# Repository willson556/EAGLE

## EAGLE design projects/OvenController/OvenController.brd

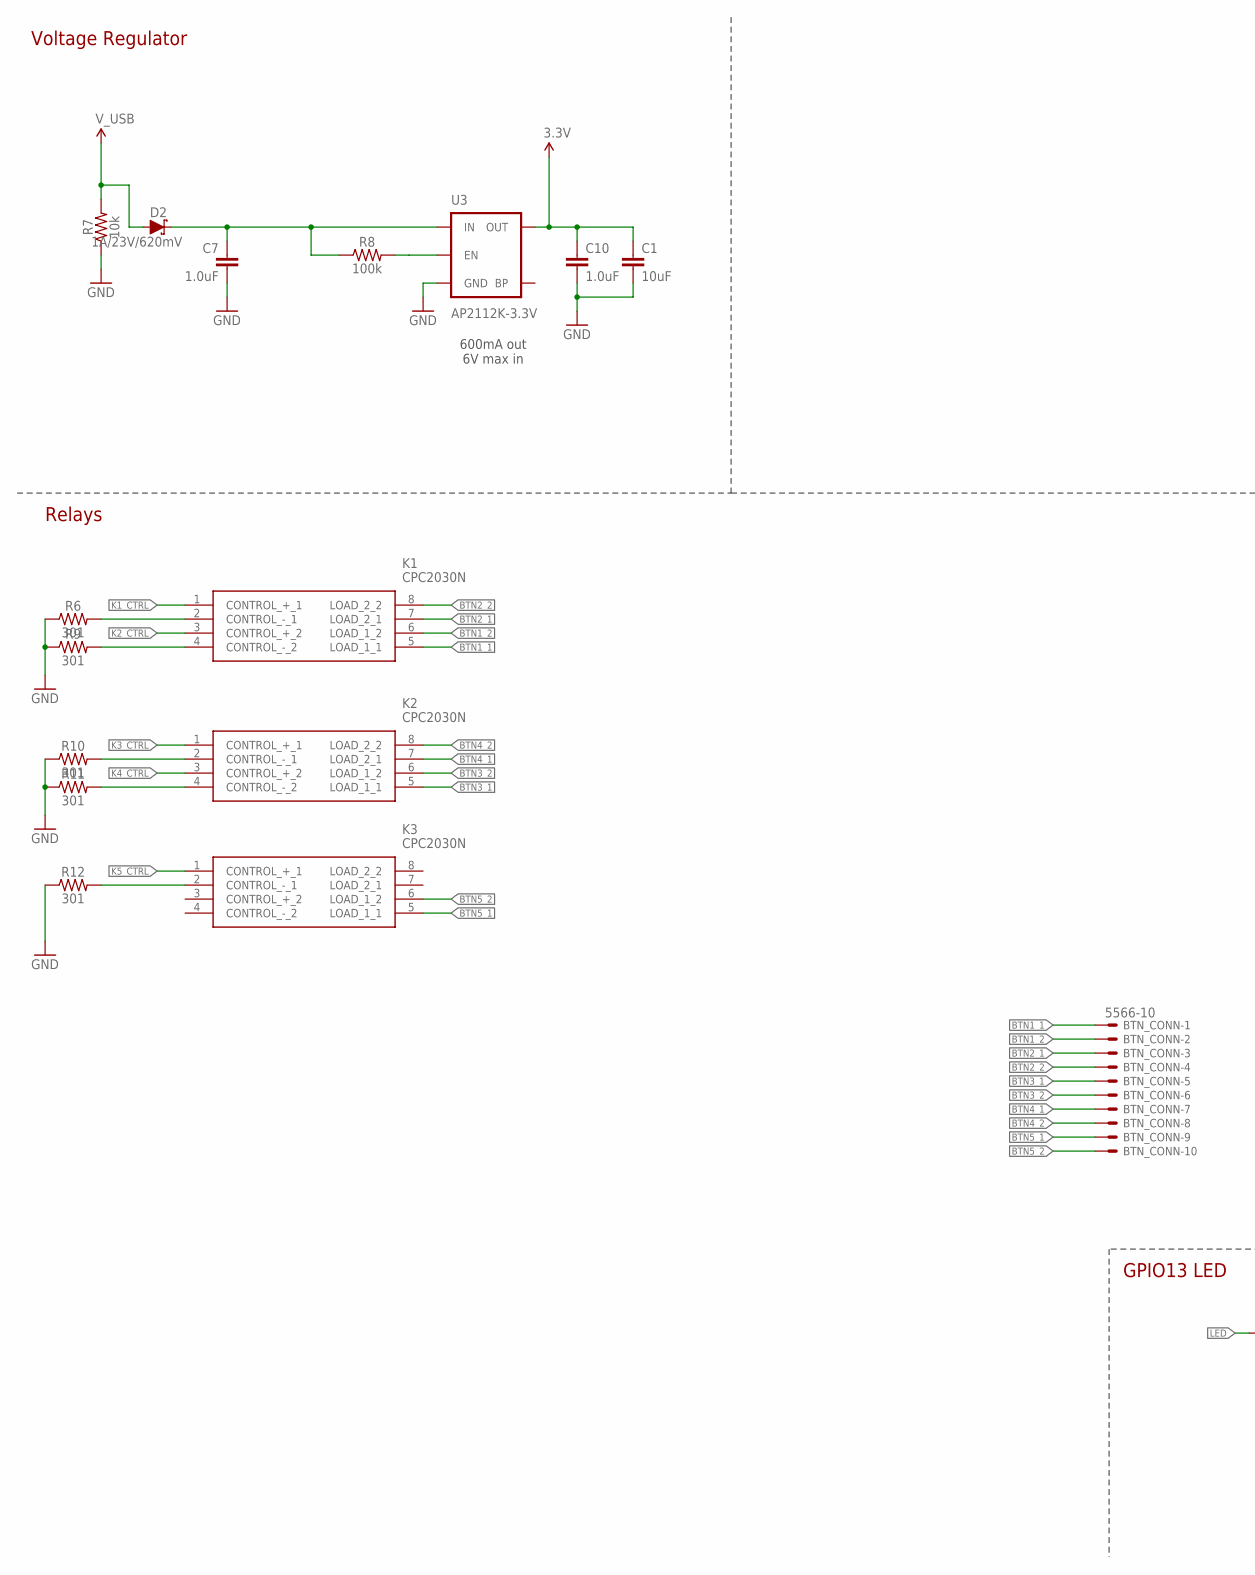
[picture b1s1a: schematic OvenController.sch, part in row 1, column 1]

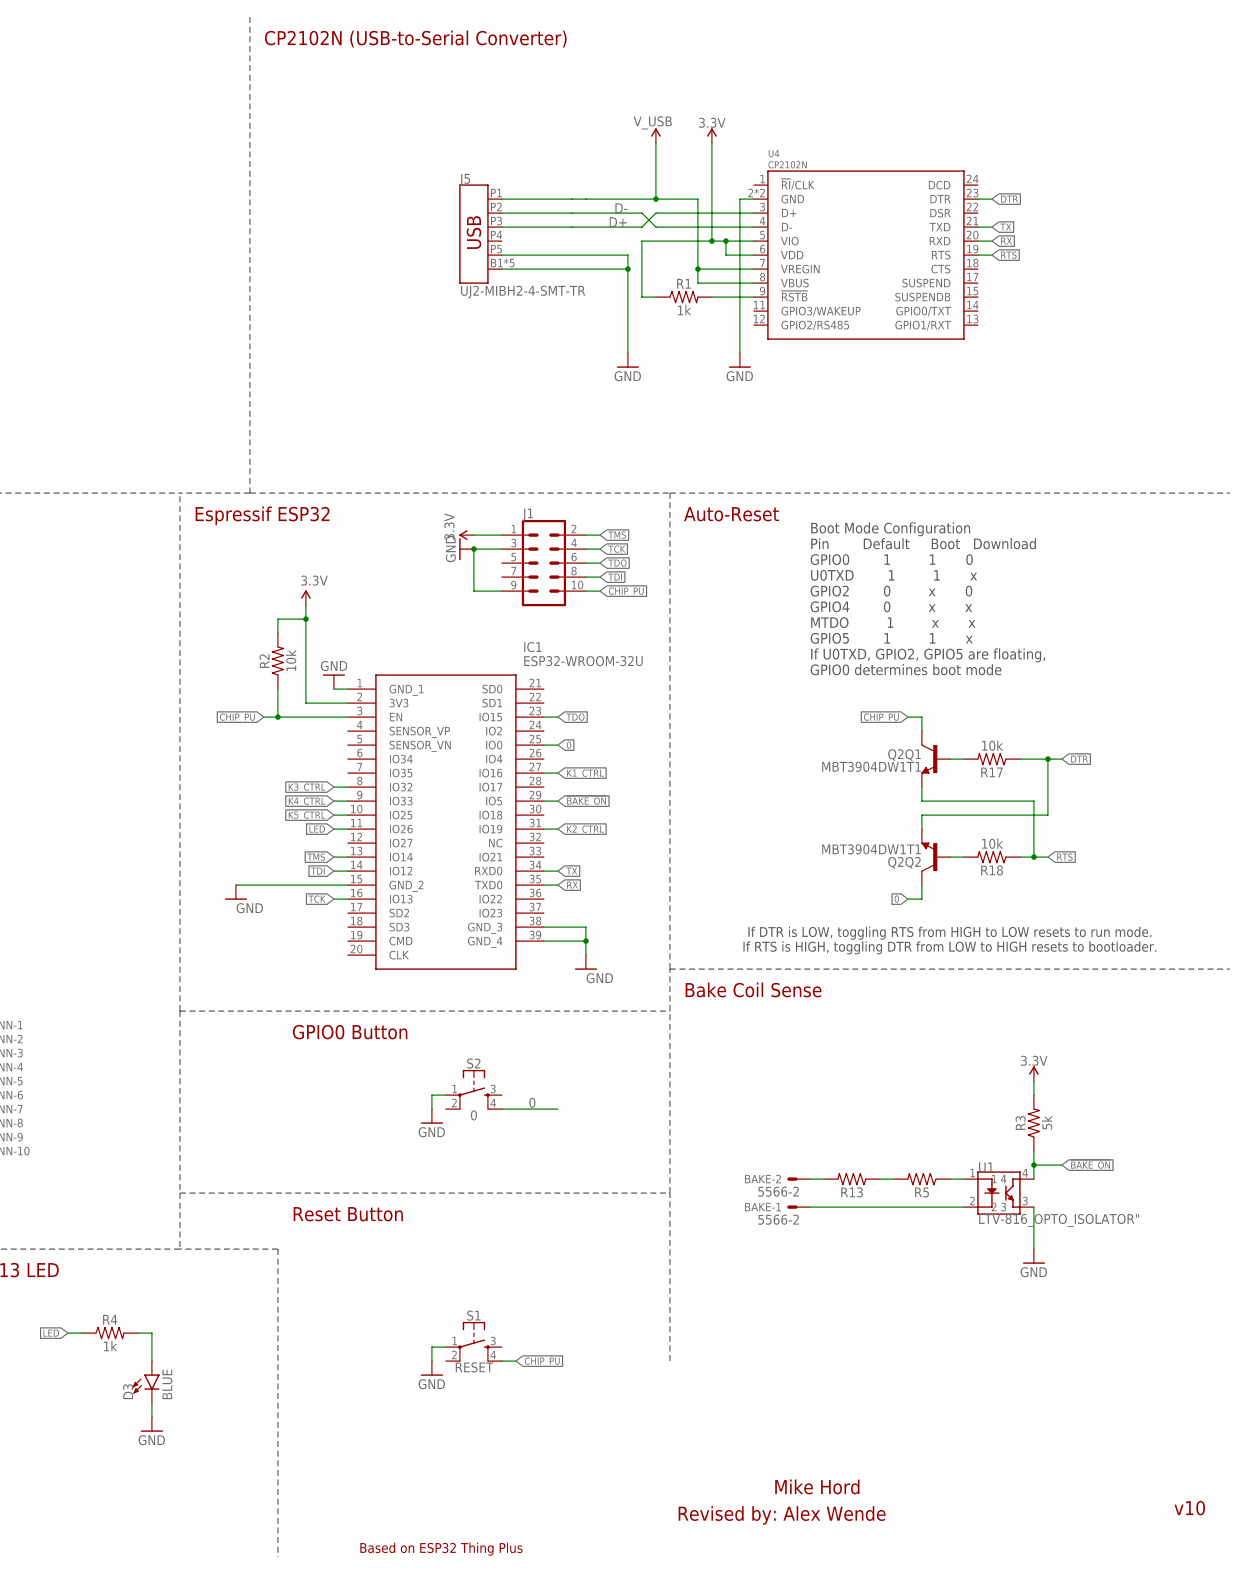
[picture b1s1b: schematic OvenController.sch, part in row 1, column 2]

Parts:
BAKE: 5566-2
BTN_CONN: 5566-10
C1: 10uF; 0603
C7, C10: 1.0uF; 0603
D2: 1A/23V/620mV; SOD-323
D3: BLUE; LED-0603
IC1: ESP32-WROOM-32U; ESP32WROOM32D
J1: CONN_05X2PTH; 2X5
J5: UJ2-MIBH2-4-SMT-TR
K1, K2, K3: CPC2030N; SOP254P610X218-8N
Q2: MBT3904DW1T1; SC70-6
R1, R4: 1k; 0603
R2, R7, R17, R18: 10k; 0603
R3: 5k; 0603
R5, R13: 300; R1210W
R6, R9, R10, R11, R12: 301; 0603
R8: 100k; 0603
S1: RESET; TACTILE_SWITCH_SMD_4.6X2.8MM
S2: 0; TACTILE_SWITCH_SMD_4.6X2.8MM
U1: LTV-816_OPTO_ISOLATOR"; LTV-816_4PIN_DIP
U3: AP2112K-3.3V; SOT23-5
U4: CP2102N; QFN24

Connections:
0: IC1.25 (IO0), Q2.6 (C), S2.4
3.3V: C1.1, C10.1, IC1.2 (3V3), J1.1, R1.1, R2.2, R3.2, U3.5 (OUT), U4.5 (VIO), U4.6 (VDD)
!BAKE_ON: IC1.29 (IO5), R3.1, U1.4
BTN1_1: BTN_CONN.1, K1.5 (LOAD_1_1)
BTN1_2: BTN_CONN.2, K1.6 (LOAD_1_2)
BTN2_1: BTN_CONN.3, K1.7 (LOAD_2_1)
BTN2_2: BTN_CONN.4, K1.8 (LOAD_2_2)
BTN3_1: BTN_CONN.5, K2.5 (LOAD_1_1)
BTN3_2: BTN_CONN.6, K2.6 (LOAD_1_2)
BTN4_1: BTN_CONN.7, K2.7 (LOAD_2_1)
BTN4_2: BTN_CONN.8, K2.8 (LOAD_2_2)
BTN5_1: BTN_CONN.9, K3.5 (LOAD_1_1)
BTN5_2: BTN_CONN.10, K3.6 (LOAD_1_2)
CHIP_PU: IC1.3 (EN), J1.10, Q2.3 (C), R2.1, S1.4
CONTROL_+_2: K3.3 (CONTROL_+_2)
CONTROL_-_2: K3.4 (CONTROL_-_2)
D+: J5.P3 (D+), U4.3 (D+)
D-: J5.P2 (D-), U4.4 (D-)
DTR: Q2.1 (E), R17.1, U4.23 (DTR)
EN: R8.2, U3.3 (EN)
GND: C1.2, C7.2, C10.2, D3.C, IC1.1 (GND_1), IC1.15 (GND_2), IC1.38 (GND_3), IC1.39 (GND_4), J1.3, J1.9, J5.B1 (SHIELD), J5.B2 (SHIELD), J5.B3 (SHIELD), J5.B4 (SHIELD), J5.B5 (SHIELD), J5.P5 (GND), R6.1, R7.1, R9.1, R10.1, R11.1, R12.1, S1.1, S2.1, U1.3, U3.2 (GND), U4.2 (GND), U4.PAD (GND)
K1_CTRL: IC1.27 (IO16), K1.1 (CONTROL_+_1)
K2_CTRL: IC1.31 (IO19), K1.3 (CONTROL_+_2)
K3_CTRL: IC1.8 (IO32), K2.1 (CONTROL_+_1)
K4_CTRL: IC1.9 (IO33), K2.3 (CONTROL_+_2)
K5_CTRL: IC1.10 (IO25), K3.1 (CONTROL_+_1)
LED: IC1.11 (IO26), R4.1
unnamed: R1.2, U4.9 (!RSTB)
unnamed: D3.A, R4.2
unnamed: C7.1, D2.C, R8.1, U3.1 (IN)
unnamed: BAKE.2, R13.2
unnamed: R5.2, R13.1
unnamed: BAKE.1, U1.2
unnamed: R5.1, U1.1
unnamed: K1.2 (CONTROL_-_1), R6.2
unnamed: K1.4 (CONTROL_-_2), R9.2
unnamed: Q2.5 (B), R17.2
unnamed: K2.2 (CONTROL_-_1), R10.2
unnamed: Q2.2 (B), R18.2
unnamed: K2.4 (CONTROL_-_2), R11.2
unnamed: K3.2 (CONTROL_-_1), R12.2
RTS: Q2.4 (E), R18.1, U4.19 (RTS)
RX: IC1.35 (TXD0), U4.20 (RXD)
TCK: IC1.16 (IO13), J1.4
TDI: IC1.14 (IO12), J1.8
TDO: IC1.23 (IO15), J1.6
TMS: IC1.13 (IO14), J1.2
TX: IC1.34 (RXD0), U4.21 (TXD)
V_USB: D2.A, J5.P1 (VBUS), R7.2, U4.7 (VREGIN), U4.8 (VBUS)

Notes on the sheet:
Boot Mode Configuration Pin Default Boot Download GPIO0 1 1 0 U0TXD 1 1 x GPIO2 0 x 0 GPIO4 0 x x MTDO 1 x x GPIO5 1 1 x If U0TXD, GPIO2, GPIO5 are floating, GPIO0 determines boot mode
CP2102N (USB-to-Serial Converter)
Voltage Regulator
600mA out 6V max in
Auto-Reset
Espressif ESP32
Reset Button
v10
Based on ESP32 Thing Plus
If DTR is LOW, toggling RTS from HIGH to LOW resets to run mode. If RTS is HIGH, toggling DTR from LOW to HIGH resets to bootloader.
Mike Hord
GPIO13 LED
GPIO0 Button
Revised by: Alex Wende
Relays
Bake Coil Sense

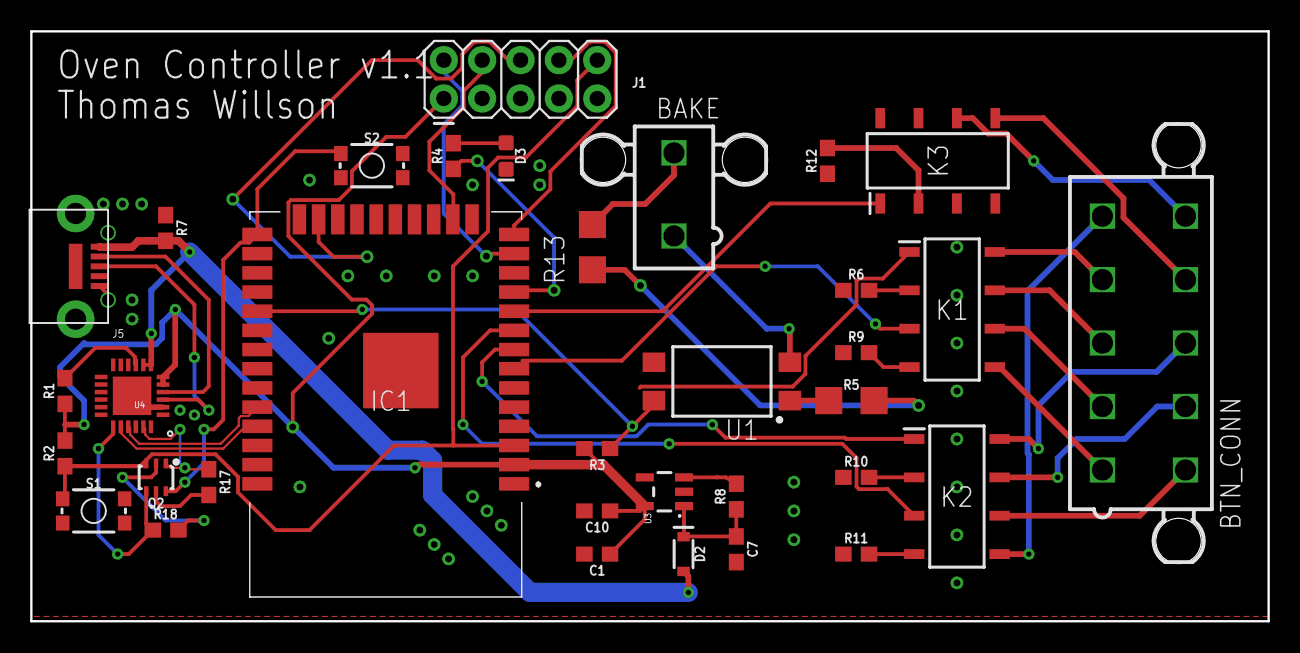
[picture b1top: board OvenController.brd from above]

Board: 2 copper layers, 81.9 x 39.1 mm, 34 parts (0 on the bottom side), 47 nets.

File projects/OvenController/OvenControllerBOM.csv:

Qty,Value,Device,In Cart,Package,Parts,Description,DESCRIPTION2,HEIGHT,MANUFACTURER_NAME,MANUFACTURER_PART_NUMBER,MF,MOUSER_PART_NUMBER,MOUSER_PRICE-STOCK,MPN,OC_FARNELL,OC_NEWARK,PROD_ID,RS_PART_NUMBER,RS_PRICE-STOCK,SPICEPREFIX,VALUE3
1,,USB_MICRO-B_HALF_PTH_MILL,x,USB-MICROB-PTH-MILL,J5,USB Type Micro-B Connector,,,,,,,,,,,CONN-13711,,,,
1,0,MOMENTARY-SWITCH-SPST-2-SMD-4.6X2.8MM,x,TACTILE_SWITCH_SMD_4.6X2.8MM,S2,Momentary Switch (Pushbutton) - SPST - Two Circuits,,,,,,,,,,,SWCH-13065,,,,
1,1.0uF,1.0UF-0402-16V-10%,x,402,C10,1µF ceramic capacitors,,,,,,,,,,,CAP-12417,,,,1.0uF
1,1.0uF,1.0UF-0603-16V-10%-X7R,x,603,C7,1µF ceramic capacitors,,,,,,,,,,,CAP-13930,,,,1.0uF
1,100K,100KOHM-0603-1/16W-1%,x,603,R8,100kΩ resistor,,,,,,,,,,,RES-13495,,,,100K
4,10k,10KOHM-0603-1/10W-1%,x,603,R2,,,,,,,,,,,,,,,,
1,10uF,10UF-0603-6.3V-20%,x,603,C1,10.0µF ceramic capacitors,,,,,,,,,,,CAP-11015,,,,10uF
1,1A/23V/620mV,DIODE-SCHOTTKY-BAT20J,x,SOD-323,D2,Schottky diode,,,,,,,,,,,DIO-11623,,,,1A/23V/620mV
2,1k,1KOHM-0603-1/10W-1%,x,603,R1,,,,,,,,,,,,,,,,
2,300,R-US_R1210W,x,R1210W,R5,,,,,,,,,,,,,,,,
5,301,RESISTOR0603,x,603,R6,,,,,,,,,,,,,,,,
1,5566-10,5566-10,x,5566-10,BTN_CONN,Mini FIT connector 10 pol,,,,,MOLEX,,,,unknown,unknown,,,,,
1,5566-2,5566-2,x,5566-2,BAKE,Mini FIT connector 2 pol,,,,39-30-6025,MOLEX,,,,1822072,unknown,,,,,
1,5k,RESISTOR0603,x,603,R3,Generic Resistor Package,,,,,,,,,,, ,,,, 
1,AP2112K-3.3V,V_REG_LDOSMD,x,SOT23-5,U3,Voltage Regulator LDO,,,,,,,,,,,VREG-12457,,,,
1,BLUE,LED-BLUE0603,x,LED-0603,D3,Blue SMD LED,,,,,,,,,,,DIO-08575,,,,BLUE
1,CP2102N,CP2102N,x,QFN24,U4,,,,,,,,,,,,IC-14020,,,,
3,CPC2030N,CPC2030N,x,SOP254P610X218-8N,K1,,,,,,,,,,,,,,,,
1,ESP32-WROOM-32U,ESP32-WROOM-32U,x,ESP32WROOM32D,IC1,WiFi Modules (802.11) SMD Module,,,,,,,,,,,,,,,
1,"LTV-816_OPTO_ISOLATOR"";LTV-816_OPTO_ISOLATOR""""",LTV-816_4PIN_DIP,x,U1,,,,,,,,,,,,IC-14145,,,,,
1,MBT3904DW1T1,TRANS_NPN_DUAL-MBT3904DW1T1,x,SC70-6,Q2,Dual NPN Transistors in Single Package,,,,,,,,,,,TRANS-13337,,,,
1,RESET,MOMENTARY-SWITCH-SPST-2-SMD-4.6X2.8MM,x,TACTILE_SWITCH_SMD_4.6X2.8MM,S1,Momentary Switch (Pushbutton) - SPST - Two Circuits,,,,,,,,,,,SWCH-13065,,,,

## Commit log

2019-04-19 Initial import
2019-04-19 Add .gitignore.
2019-04-19 Add Sparkfun Eagle Libraries.
2019-04-19 Start HW Design
2019-04-20 Ignore `.DS_Store` files.
2019-04-20 Add SamacSys tool and import ESP32-WROOM-32U.
2019-04-20 Start with SparkFun Thing Plus schematic and board.
2019-04-20 Remove board file.
2019-04-20 Initial draft of schematic and part way through PCB layout.
2019-04-20 Updated schematic and semi-final layout.
2019-04-21 OvenController v1.0 as ordered.
2019-04-21 Oven Controller v1.1
    Added JTAG header.
2019-05-03 Schematic revisions based on build. Layout needs update.

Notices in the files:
parts and their libraries:
SparkFun-Capacitors: Licensing: Creative Commons ShareAlike 4.0 International - https://creativecommons.org/licenses/by-sa/4.0
